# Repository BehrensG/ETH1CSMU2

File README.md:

# ETH1CSMU2
> Yet another poor man's SMU based on LT1970 Power Op Amp.

## What is a SMU ?

A Source Measurement Unit (SMU) is a versatile electronic instrument used in various applications, particularly in the field of electronics testing and characterization. It combines the functionalities of both a voltage source and a current measurement device.

## What is ETH1CSMU2 ?

ETH1CSMU2 is an ongoing hobby project focused on the development of a cost-effective Source Measurement Unit (SMU). The PCB has been designed in accordance with the Eurocard standard size, measuring 160x100 mm. It should be noted that the PCB is intended for integration with a Backplane, such as the [DIN41612_Backplane](https://github.com/BehrensG/DIN41612_Backplane), and is not intended for standalone operation (but it can be).
The PCB requires 24V DC supply. The device can sink and source voltage and current. Can generate a AC sine signal. The PCB includes pars of two ADCs for measurements. 2xADS868 designed the DC output mode, 2xAD7980 designed for AC output mode.

## Parameters

### DC
- Voltage output 11V (bipolar)
- Minimal set voltage step 1mV
- Current ranges 200uA, 2mA, 20mA and 200mA (bipolar)

### AC

- Sine wave generator
- Amplitude 6 V (bipolar)
- Offset 11 V (bipolar)
- Frequency 200 kHz

## Resources
- SCPI parser - https://github.com/j123b567/scpi-parser
- KiCAD - https://www.kicad.org
- STM32CubeIDE - https://www.st.com/en/development-tools/stm32cubeide.html
- POOR MAN'S SMU - https://poormanssmu.wordpress.com
- FreeRTOS - https://www.freertos.org/

## Images
<p align="center"> ETH1CSMU2 </p>

<p align="center"> Examples of the output voltages </p>

## Status

Project is ongoing. 

#### TBD:
1. Missing code for ADCs calibration.
2. Missing code for the trigger circuit. 
3. Need to improve the AC code.
4. More images in this README file.
5. Missing SCPI commands documentation.

**<span style="color:red">NOTE</span>**: When using KiCAD project it will be required to change the schematic and PCB libraries paths.

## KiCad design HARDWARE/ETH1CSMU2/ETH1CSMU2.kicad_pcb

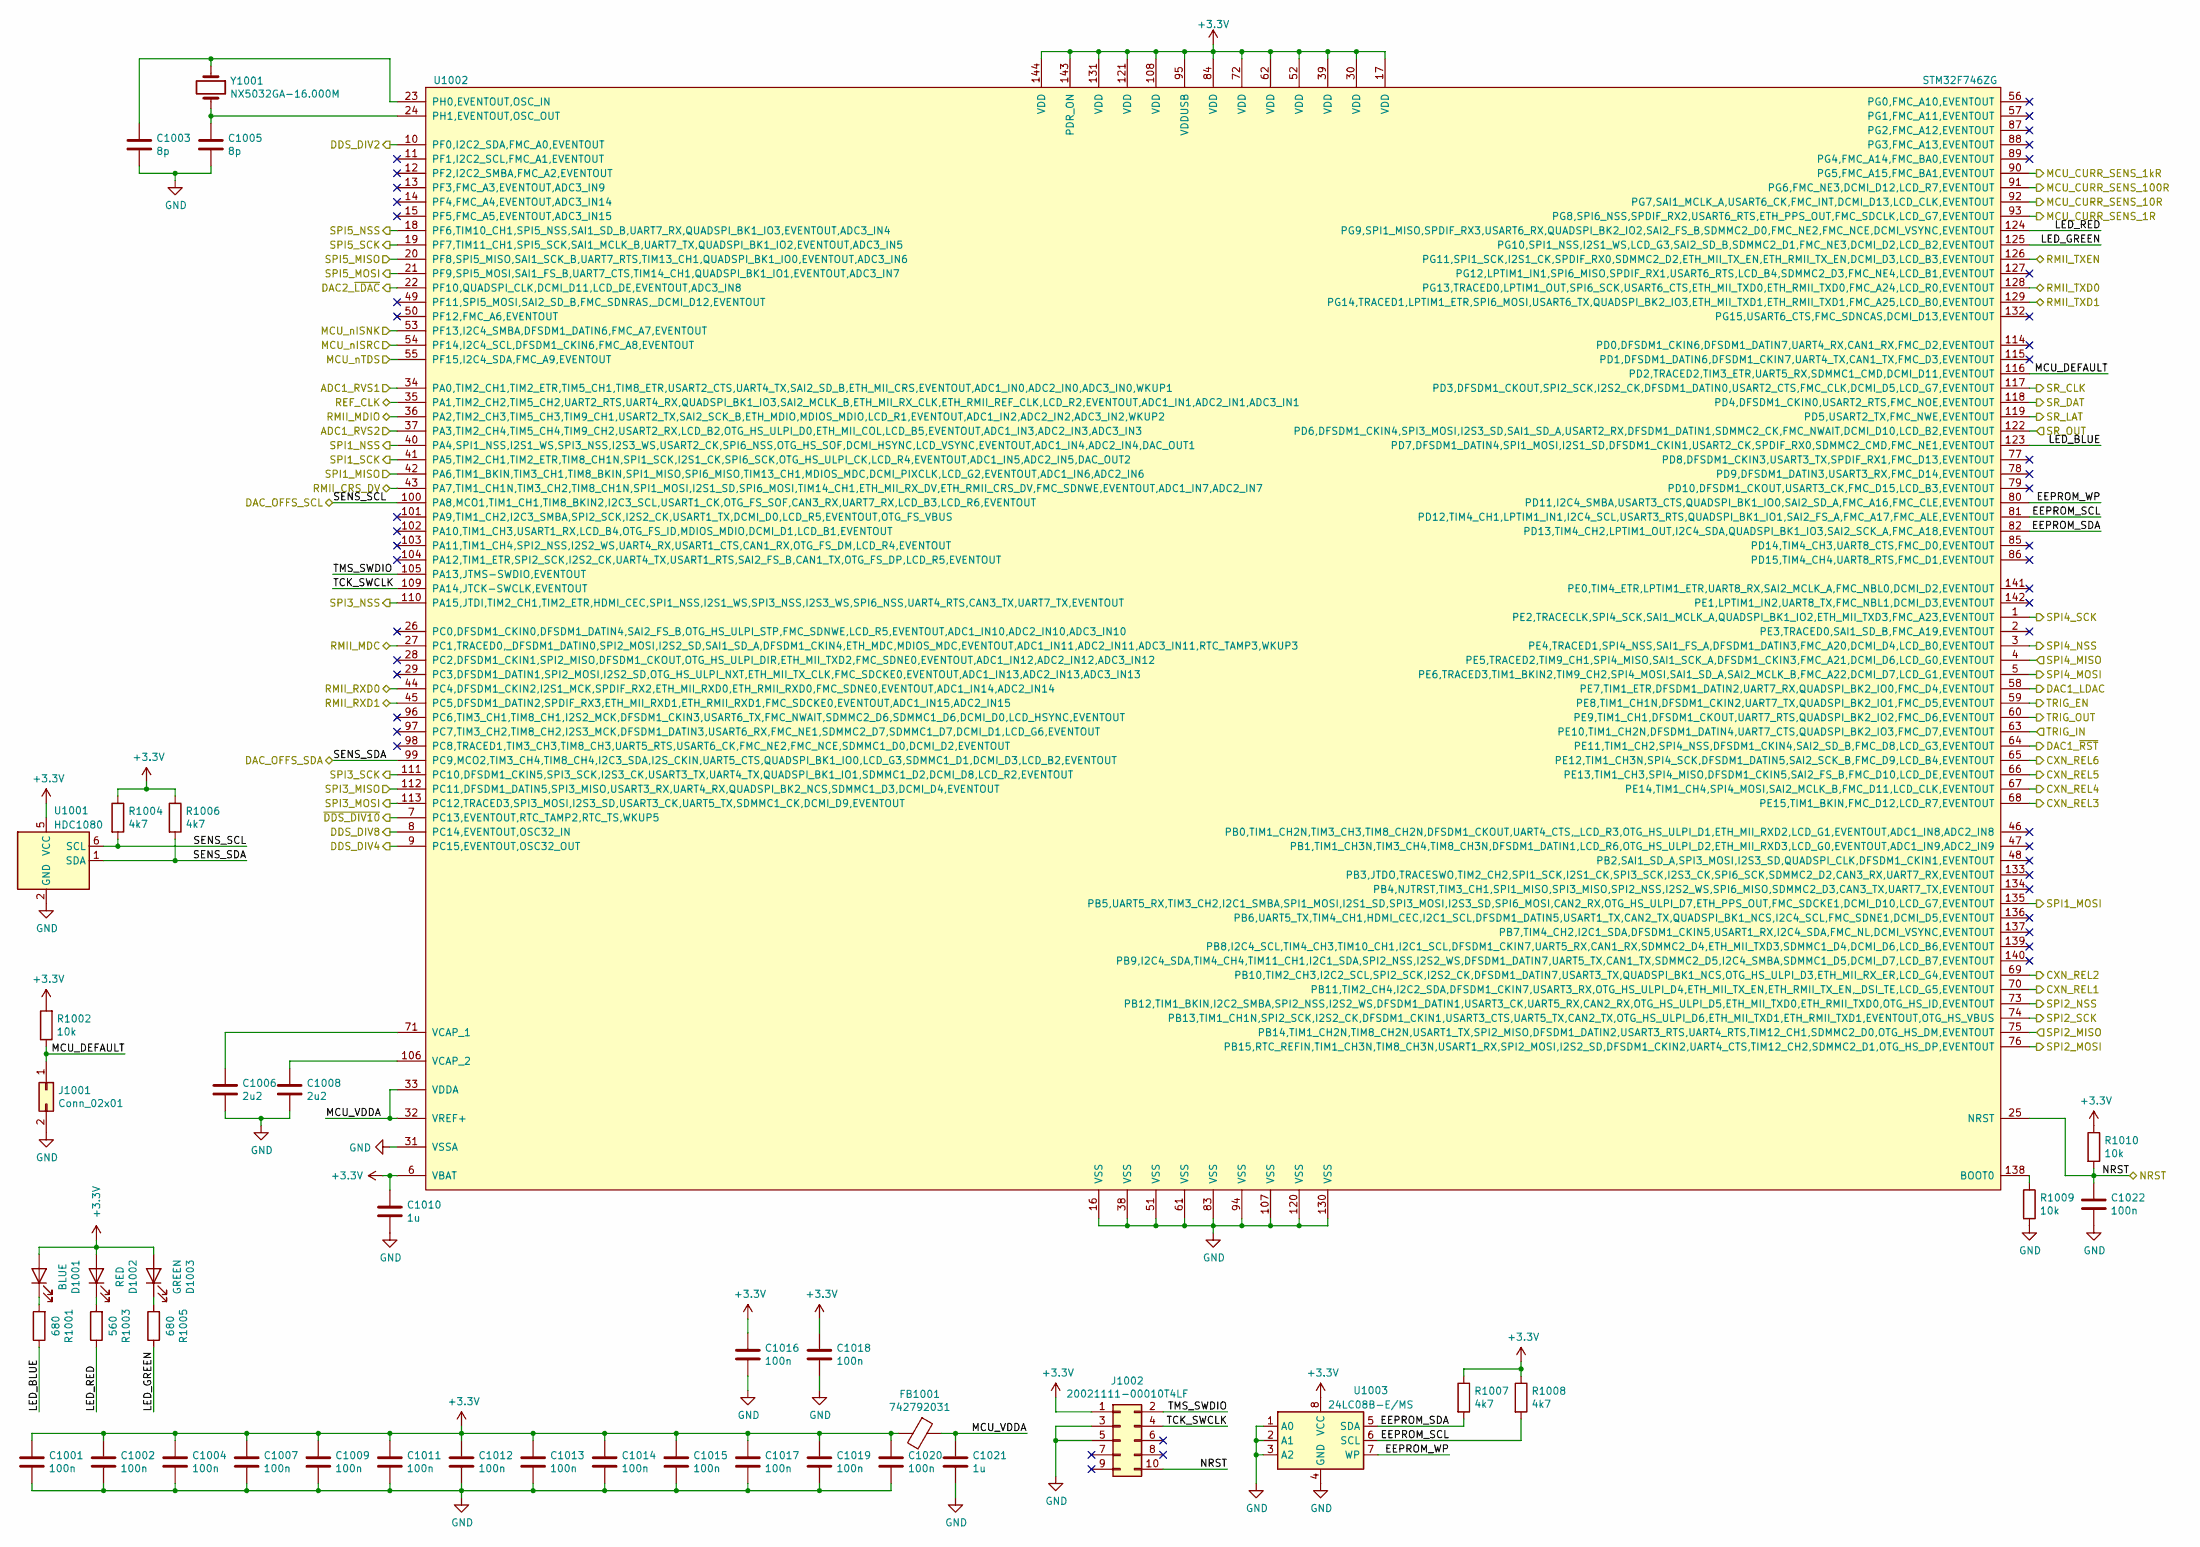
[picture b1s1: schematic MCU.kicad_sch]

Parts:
C1001, C1002, C1004, C1007, C1009, C1011, C1012, C1013, C1014, C1015, C1016, C1017, C1018, C1019, C1020, C1022: 100n; C_0603_1608Metric_Pad1.08x0.95mm_HandSolder
C1003, C1005: 8p; C_0603_1608Metric_Pad1.08x0.95mm_HandSolder
C1006, C1008: 2u2; C_0603_1608Metric_Pad1.08x0.95mm_HandSolder
C1010, C1021: 1u; C_0603_1608Metric_Pad1.08x0.95mm_HandSolder
D1001: BLUE; LED_0603_1608Metric_Pad1.05x0.95mm_HandSolder
D1002: RED; LED_0603_1608Metric_Pad1.05x0.95mm_HandSolder
D1003: GREEN; LED_0603_1608Metric_Pad1.05x0.95mm_HandSolder
FB1001: 742792031; L_0805_2012Metric_Pad1.15x1.40mm_HandSolder
J1001: Conn_02x01; PinHeader_1x02_P2.54mm_Vertical
J1002: 20021111-00010T4LF; PinHeader_2x05_P1.27mm_Vertical
R1001, R1005: 680; R_0603_1608Metric_Pad0.98x0.95mm_HandSolder
R1002, R1009, R1010: 10k; R_0603_1608Metric_Pad0.98x0.95mm_HandSolder
R1003: 560; R_0603_1608Metric_Pad0.98x0.95mm_HandSolder
R1004, R1006, R1007, R1008: 4k7; R_0603_1608Metric_Pad0.98x0.95mm_HandSolder
U1001: HDC1080; Texas_PWSON-N6
U1002: STM32F746ZG; TQFP-144_20x20mm_P0.5mm
U1003: 24LC08B-E/MS; MSOP-8_3x3mm_P0.65mm
Y1001: NX5032GA-16.000M; NX3225GD

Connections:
/Connect/CXN_REL1: U1002.70 (PB11,TIM2_CH4,I2C2_SDA,DFSDM1_CKIN7,USA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); also elsewhere on the board
/Connect/CXN_REL2: U1002.69 (PB10,TIM2_CH3,I2C2_SCL,SPI2_SCK,I2S2_CK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); also elsewhere on the board
/Connect/CXN_REL3: U1002.68 (PE15,TIM1_BKIN,FMC_D12,LCD_R7,EVENTOUT); also elsewhere on the board
/Connect/CXN_REL4: U1002.67 (PE14,TIM1_CH4,SPI4_MOSI,SAI2_MCLK_B,FMC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); also elsewhere on the board
/Connect/CXN_REL5: U1002.66 (PE13,TIM1_CH3,SPI4_MISO,DFSDM1_CKIN5,SA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); also elsewhere on the board
/Connect/CXN_REL6: U1002.65 (PE12,TIM1_CH3N,SPI4_SCK,DFSDM1_DATIN5,S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); also elsewhere on the board
/Control/SR_CLK: U1002.117 (PD3,DFSDM1_CKOUT,SPI2_SCK,I2S2_CK,DFSDM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); also elsewhere on the board
/Control/SR_DAT: U1002.118 (PD4,DFSDM1_CKIN0,USART2_RTS,FMC_NOE,EVE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); also elsewhere on the board
/Control/SR_LAT: U1002.119 (PD5,USART2_TX,FMC_NWE,EVENTOUT); also elsewhere on the board
/Control/SR_OUT: U1002.122 (PD6,DFSDM1_CKIN4,SPI3_MOSI,I2S3_SD,SAI1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); also elsewhere on the board
/Ethernet/MDIO: U1002.36 (PA2,TIM2_CH3,TIM5_CH3,TIM9_CH1,USART2_T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); also elsewhere on the board
/Ethernet/REF_CLK: U1002.35 (PA1,TIM2_CH2,TIM5_CH2,UART2_RTS,UART4_R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); also elsewhere on the board
/Ethernet/RMII_CRS_DV: U1002.43 (PA7,TIM1_CH1N,TIM3_CH2,TIM8_CH1N,SPI1_M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); also elsewhere on the board
/Ethernet/RMII_MDC: U1002.27 (PC1,TRACED0,_DFSDM1_DATIN0,SPI2_MOSI,I2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); also elsewhere on the board
/Ethernet/RMII_RXD0: U1002.44 (PC4,DFSDM1_CKIN2,I2S1_MCK,SPDIF_RX2,ETH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); also elsewhere on the board
/Ethernet/RMII_RXD1: U1002.45 (PC5,DFSDM1_DATIN2,SPDIF_RX3,ETH_MII_RXD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); also elsewhere on the board
/Ethernet/RMII_TXD0: U1002.128 (PG13,TRACED0,LPTIM1_OUT,SPI6_SCK,USART6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); also elsewhere on the board
/Ethernet/RMII_TXD1: U1002.129 (PG14,TRACED1,LPTIM1_ETR,SPI6_MOSI,USART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); also elsewhere on the board
/Ethernet/RMII_TXEN: U1002.126 (PG11,SPI1_SCK,I2S1_CK,SPDIF_RX0,SDMMC2_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); also elsewhere on the board
/Frontend/MCU_CURR_SENS_1R: U1002.93 (PG8,SPI6_NSS,SPDIF_RX2,USART6_RTS,ETH_P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); also elsewhere on the board
/Frontend/MCU_CURR_SENS_1kR: U1002.90 (PG5,FMC_A15,FMC_BA1,EVENTOUT); also elsewhere on the board
/Frontend/MCU_CURR_SENS_10R: U1002.92 (PG7,SAI1_MCLK_A,USART6_CK,FMC_INT,DCMI_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); also elsewhere on the board
/Frontend/MCU_CURR_SENS_100R: U1002.91 (PG6,FMC_NE3,DCMI_D12,LCD_R7,EVENTOUT); also elsewhere on the board
/Frontend/MCU_nISNK: U1002.53 (PF13,I2C4_SMBA,DFSDM1_DATIN6,FMC_A7,EVE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); also elsewhere on the board
/Frontend/MCU_nISRC: U1002.54 (PF14,I2C4_SCL,DFSDM1_CKIN6,FMC_A8,EVENT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); also elsewhere on the board
/Frontend/MCU_nTDS: U1002.55 (PF15,I2C4_SDA,FMC_A9,EVENTOUT); also elsewhere on the board
/MCU/ADC1_RVS1: U1002.34 (PA0,TIM2_CH1,TIM2_ETR,TIM5_CH1,TIM8_ETR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); also elsewhere on the board
/MCU/ADC1_RVS2: U1002.37 (PA3,TIM2_CH4,TIM5_CH4,TIM9_CH2,USART2_R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); also elsewhere on the board
/MCU/DAC1_LDAC: U1002.58 (PE7,TIM1_ETR,DFSDM1_DATIN2,UART7_RX,QUA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); also elsewhere on the board
/MCU/DAC1_~RST: U1002.64 (PE11,TIM1_CH2,SPI4_NSS,DFSDM1_CKIN4,SAI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); also elsewhere on the board
/MCU/DAC2_~LDAC: U1002.22 (PF10,QUADSPI_CLK,DCMI_D11,LCD_DE,EVENTO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); also elsewhere on the board
/MCU/DDS_DIV2: U1002.10 (PF0,I2C2_SDA,FMC_A0,EVENTOUT); also elsewhere on the board
/MCU/DDS_DIV4: U1002.9 (PC15,EVENTOUT,OSC32_OUT); also elsewhere on the board
/MCU/DDS_DIV8: U1002.8 (PC14,EVENTOUT,OSC32_IN); also elsewhere on the board
/MCU/EEPROM_SCL: R1008.2, U1002.81 (PD12,TIM4_CH1,LPTIM1_IN1,I2C4_SCL,USART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), U1003.6 (SCL)
/MCU/EEPROM_SDA: R1007.2, U1002.82 (PD13,TIM4_CH2,LPTIM1_OUT,I2C4_SDA,QUADS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), U1003.5 (SDA)
/MCU/EEPROM_WP: U1002.80 (PD11,I2C4_SMBA,USART3_CTS,QUADSPI_BK1_I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), U1003.7 (WP)
/MCU/LED_BLUE: R1001.1, U1002.123 (PD7,DFSDM1_DATIN4,SPI1_MOSI,I2S1_SD,DFS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)
/MCU/LED_GREEN: R1005.1, U1002.125 (PG10,SPI1_NSS,I2S1_WS,LCD_G3,SAI2_SD_B,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)
/MCU/LED_RED: R1003.1, U1002.124 (PG9,SPI1_MISO,SPDIF_RX3,USART6_RX,QUADS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)
/MCU/MCU_DEFAULT: J1001.1, R1002.1, U1002.116 (PD2,TRACED2,TIM3_ETR,UART5_RX,SDMMC1_CM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)
/MCU/MCU_VDDA: C1021.1, FB1001.1, U1002.32 (VREF+), U1002.33 (VDDA)
/MCU/NRST: C1022.1, J1002.10, R1010.2, U1002.25 (NRST); also elsewhere on the board
/MCU/SENS_SCL: R1004.2, U1001.6 (SCL), U1002.100 (PA8,MCO1,TIM1_CH1,TIM8_BKIN2,I2C3_SCL,U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); also elsewhere on the board
/MCU/SENS_SDA: R1006.2, U1001.1 (SDA), U1002.99 (PC9,MCO2,TIM3_CH4,TIM8_CH4,I2C3_SDA,I2S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); also elsewhere on the board
/MCU/SPI1_MISO: U1002.42 (PA6,TIM1_BKIN,TIM3_CH1,TIM8_BKIN,SPI1_M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); also elsewhere on the board
/MCU/SPI1_MOSI: U1002.135 (PB5,UART5_RX,TIM3_CH2,I2C1_SMBA,SPI1_MO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); also elsewhere on the board
/MCU/SPI1_NSS: U1002.40 (PA4,SPI1_NSS,I2S1_WS,SPI3_NSS,I2S3_WS,U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); also elsewhere on the board
/MCU/SPI1_SCK: U1002.41 (PA5,TIM2_CH1,TIM2_ETR,TIM8_CH1N,SPI1_SC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); also elsewhere on the board
/MCU/SPI2_MISO: U1002.75 (PB14,TIM1_CH2N,TIM8_CH2N,USART1_TX,SPI2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)
/MCU/SPI2_MOSI: U1002.76 (PB15,RTC_REFIN,TIM1_CH3N,TIM8_CH3N,USAR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); also elsewhere on the board
/MCU/SPI2_NSS: U1002.73 (PB12,TIM1_BKIN,I2C2_SMBA,SPI2_NSS,I2S2_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); also elsewhere on the board
/MCU/SPI2_SCK: U1002.74 (PB13,TIM1_CH1N,SPI2_SCK,I2S2_CK,DFSDM1_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); also elsewhere on the board
/MCU/SPI3_MISO: U1002.112 (PC11,DFSDM1_DATIN5,SPI3_MISO,USART3_RX,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)
/MCU/SPI3_MOSI: U1002.113 (PC12,TRACED3,SPI3_MOSI,I2S3_SD,USART3_C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); also elsewhere on the board
/MCU/SPI3_NSS: U1002.110 (PA15,JTDI,TIM2_CH1,TIM2_ETR,HDMI_CEC,SP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); also elsewhere on the board
/MCU/SPI3_SCK: U1002.111 (PC10,DFSDM1_CKIN5,SPI3_SCK,I2S3_CK,USAR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); also elsewhere on the board
/MCU/SPI4_MISO: U1002.4 (PE5,TRACED2,TIM9_CH1,SPI4_MISO,SAI1_SCK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); also elsewhere on the board
/MCU/SPI4_MOSI: U1002.5 (PE6,TRACED3,TIM1_BKIN2,TIM9_CH2,SPI4_MO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)
/MCU/SPI4_NSS: U1002.3 (PE4,TRACED1,SPI4_NSS,SAI1_FS_A,DFSDM1_D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); also elsewhere on the board
/MCU/SPI4_SCK: U1002.1 (PE2,TRACECLK,SPI4_SCK,SAI1_MCLK_A,QUADS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); also elsewhere on the board
/MCU/SPI5_MISO: U1002.20 (PF8,SPI5_MISO,SAI1_SCK_B,UART7_RTS,TIM1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)
/MCU/SPI5_MOSI: U1002.21 (PF9,SPI5_MOSI,SAI1_FS_B,UART7_CTS,TIM14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); also elsewhere on the board
/MCU/SPI5_NSS: U1002.18 (PF6,TIM10_CH1,SPI5_NSS,SAI1_SD_B,UART7_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); also elsewhere on the board
/MCU/SPI5_SCK: U1002.19 (PF7,TIM11_CH1,SPI5_SCK,SAI1_MCLK_B,UART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); also elsewhere on the board
/MCU/TCK_SWCLK: J1002.4, U1002.109 (PA14,JTCK-SWCLK,EVENTOUT)
/MCU/TMS_SWDIO: J1002.2, U1002.105 (PA13,JTMS-SWDIO,EVENTOUT)
/MCU/TRIG_EN: U1002.59 (PE8,TIM1_CH1N,DFSDM1_CKIN2,UART7_TX,QUA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); also elsewhere on the board
/MCU/TRIG_IN: U1002.63 (PE10,TIM1_CH2N,DFSDM1_DATIN4,UART7_CTS,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); also elsewhere on the board
/MCU/TRIG_OUT: U1002.60 (PE9,TIM1_CH1,DFSDM1_CKOUT,UART7_RTS,QUA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); also elsewhere on the board
/MCU/~DDS_DIV10: U1002.7 (PC13,EVENTOUT,RTC_TAMP2,RTC_TS,WKUP5); also elsewhere on the board
unnamed: C1003.1, U1002.23 (PH0,EVENTOUT,OSC_IN), Y1001.1
unnamed: C1005.1, U1002.24 (PH1,EVENTOUT,OSC_OUT), Y1001.2
unnamed: C1006.1, U1002.71 (VCAP_1)
unnamed: C1008.1, U1002.106 (VCAP_2)
unnamed: D1001.1 (K), R1001.2
unnamed: D1002.1 (K), R1003.2
unnamed: D1003.1 (K), R1005.2
unnamed: R1009.1, U1002.138 (BOOT0)

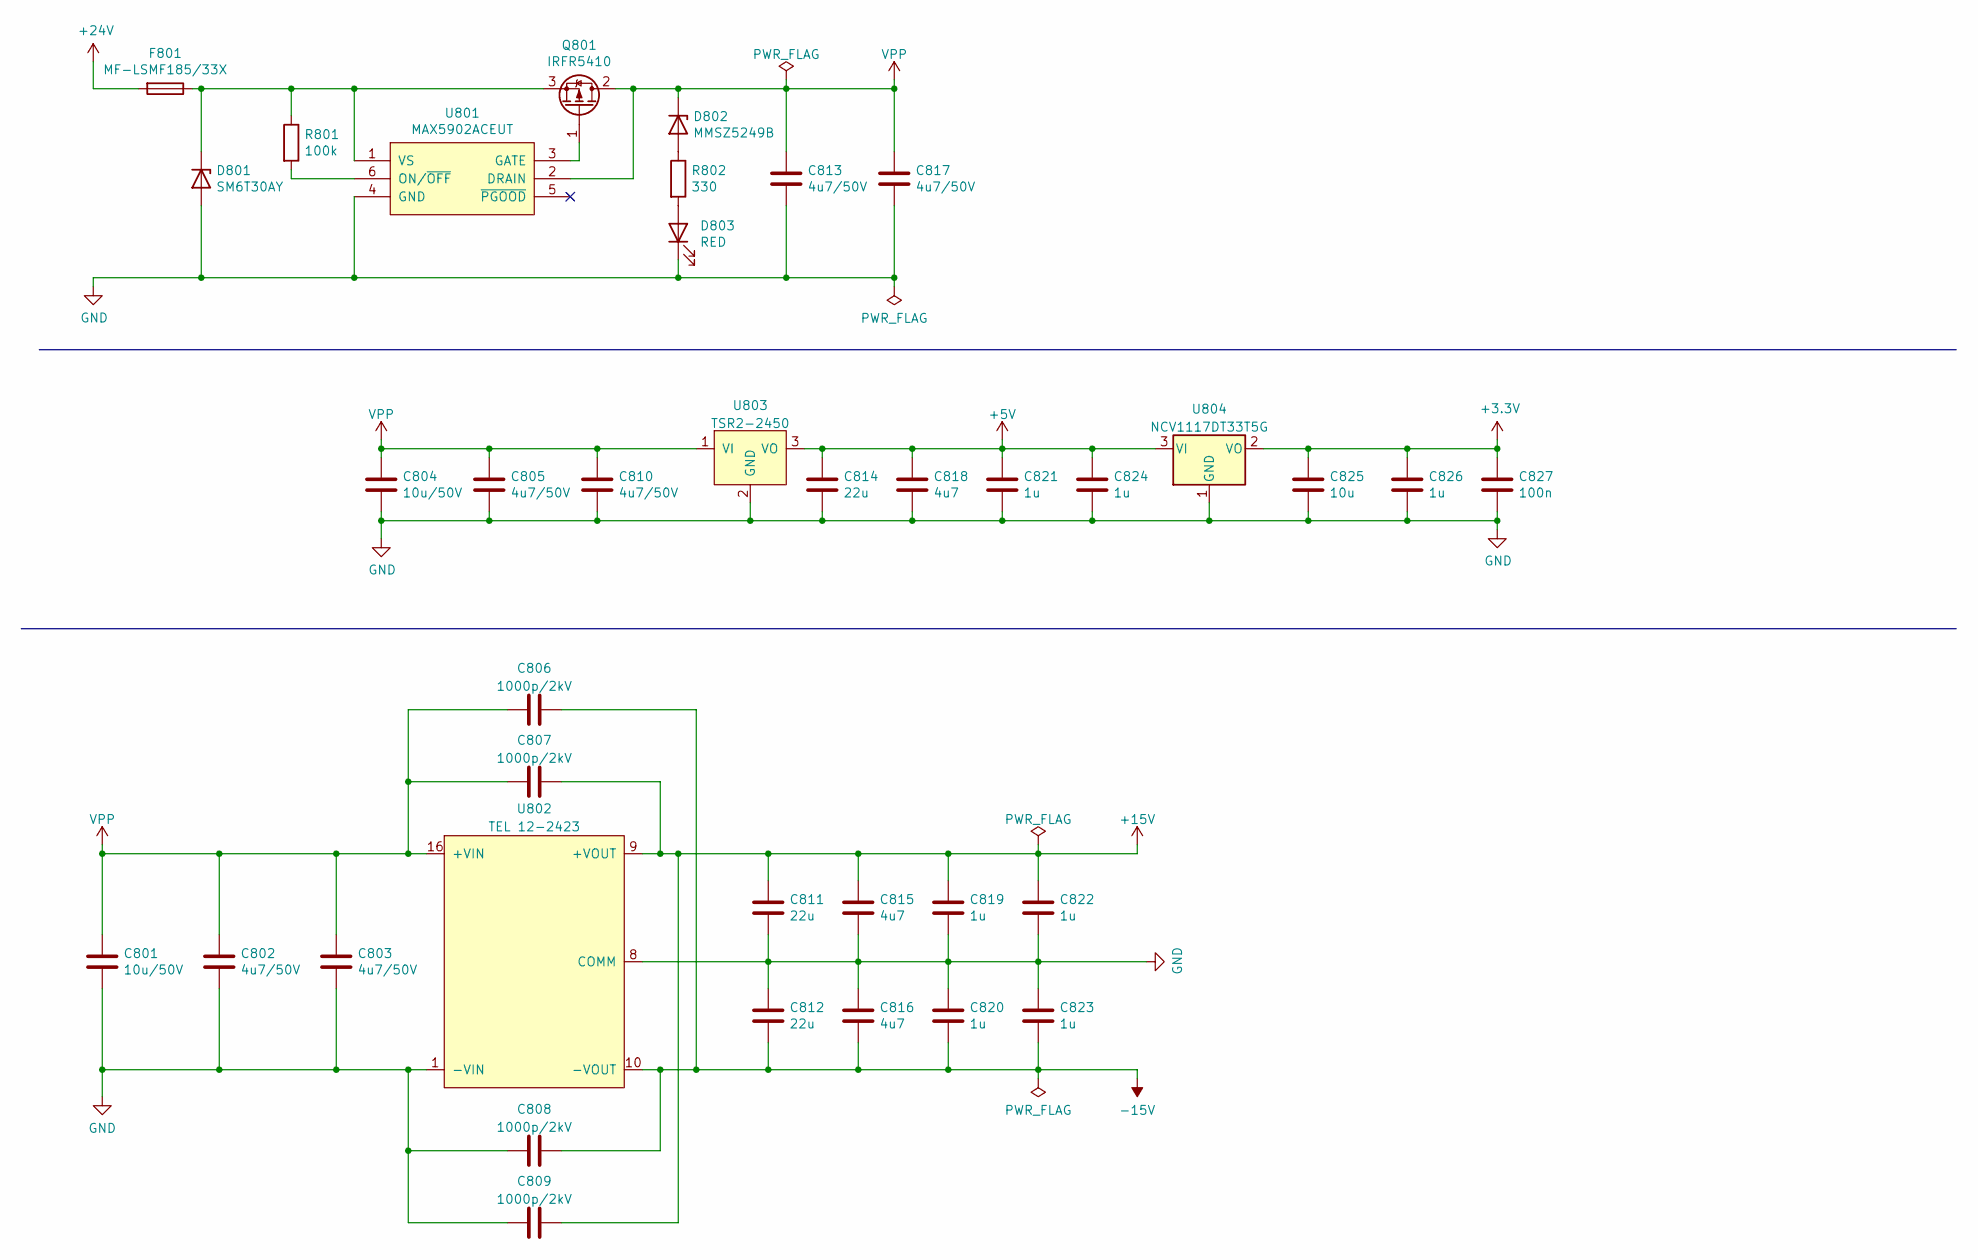
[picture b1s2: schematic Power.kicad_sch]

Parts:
C801, C804: 10u/50V; C_1206_3216Metric_Pad1.33x1.80mm_HandSolder
C802, C803, C805, C810, C813, C817: 4u7/50V; C_1206_3216Metric_Pad1.33x1.80mm_HandSolder
C806, C807, C808, C809: 1000p/2kV; C_1206_3216Metric_Pad1.33x1.80mm_HandSolder
C811, C812, C814: 22u; C_1206_3216Metric_Pad1.33x1.80mm_HandSolder
C815, C816, C818: 4u7; C_1206_3216Metric_Pad1.33x1.80mm_HandSolder
C819, C820, C821, C822, C823, C824, C826: 1u; C_1206_3216Metric_Pad1.33x1.80mm_HandSolder
C825: 10u; C_1206_3216Metric_Pad1.33x1.80mm_HandSolder
C827: 100n; C_1206_3216Metric_Pad1.33x1.80mm_HandSolder
D801: SM6T30AY; DO_214AA_REV
D802: MMSZ5249B; D_SOD-123
D803: RED; LED_0603_1608Metric_Pad1.05x0.95mm_HandSolder
F801: MF-LSMF185/33X; Fuse_SMD2920
Q801: IRFR5410; TO-252-2_Rectifier
R801: 100k; R_0603_1608Metric_Pad0.98x0.95mm_HandSolder
R802: 330; R_0603_1608Metric_Pad0.98x0.95mm_HandSolder
U801: MAX5902ACEUT; SOT-23-6_Handsoldering
U802: TEL 12-2423; TEL12-DUAL
U803: TSR2-2450; TSR2
U804: NCV1117DT33T5G; TO-252-2

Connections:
+24V: F801.2; also elsewhere on the board
unnamed: D801.1 (K), F801.1, Q801.3 (S), R801.1, U801.1 (VS)
unnamed: D802.2 (A), R802.1
unnamed: D803.2 (A), R802.2
unnamed: Q801.1 (G), U801.3 (GATE)
unnamed: R801.2, U801.6 (ON/~OFF)

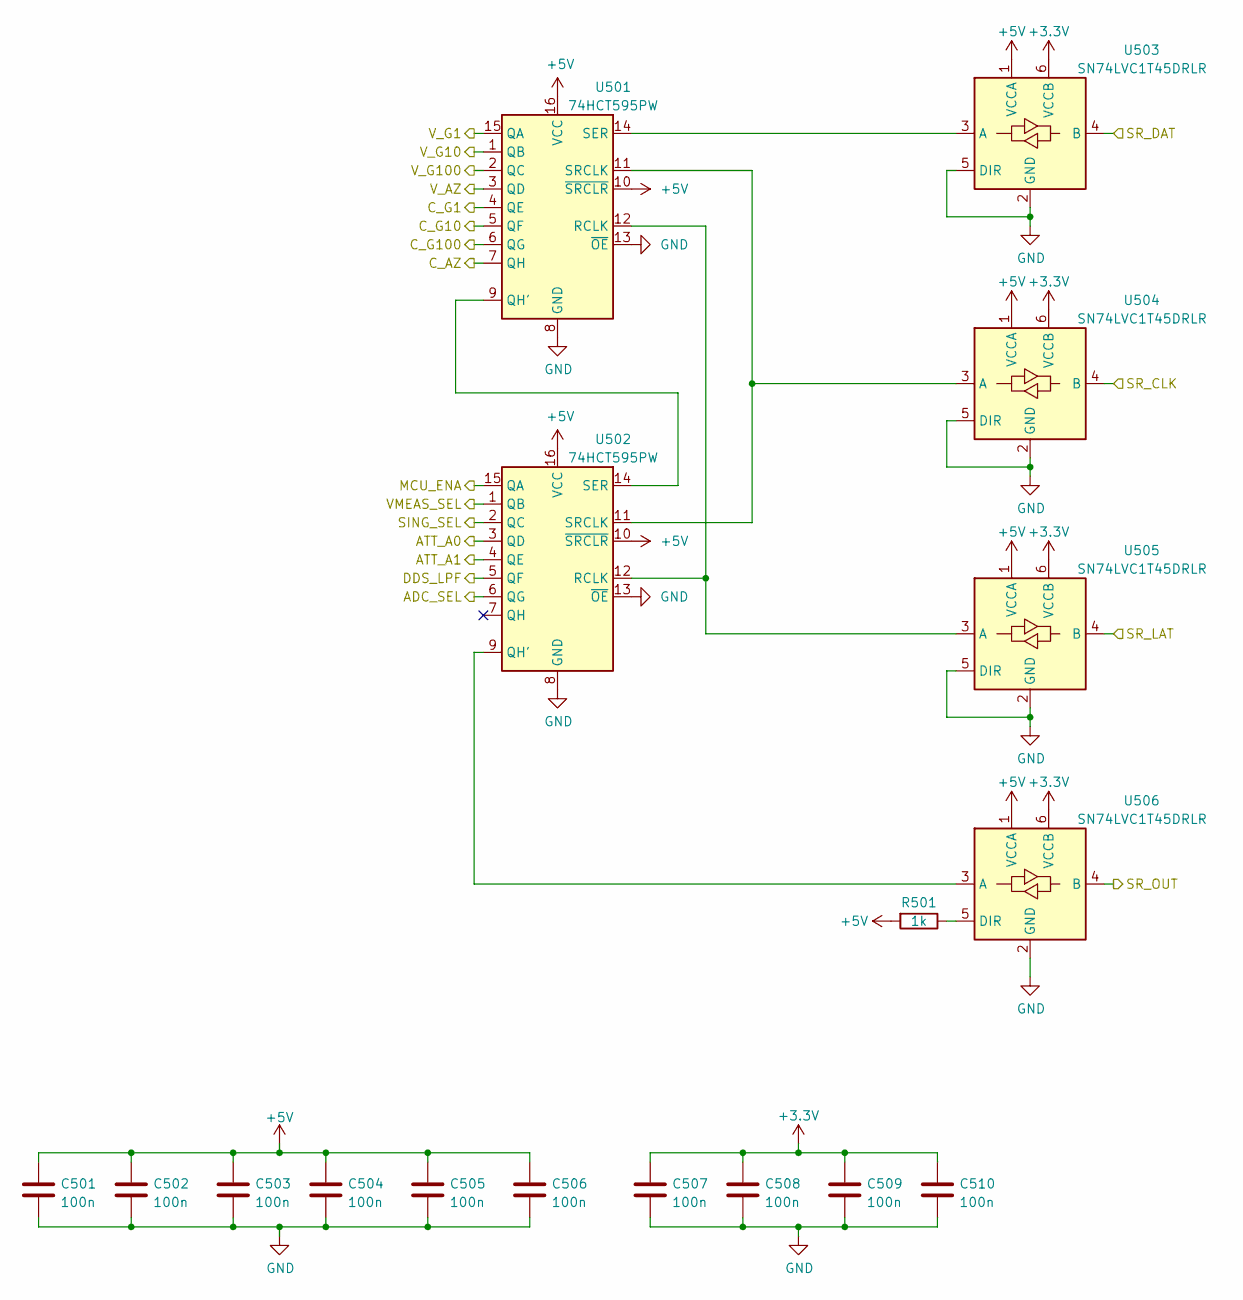
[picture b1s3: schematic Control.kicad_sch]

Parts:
C501, C502, C503, C504, C505, C506, C507, C508, C509, C510: 100n; C_0603_1608Metric_Pad1.08x0.95mm_HandSolder
R501: 1k; R_0603_1608Metric_Pad0.98x0.95mm_HandSolder
U501, U502: 74HCT595PW; TSSOP-16_4.4x5mm_P0.65mm
U503, U504, U505, U506: SN74LVC1T45DRLR; SOT-563

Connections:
/Control/ATT_A0: U502.3 (QD); also elsewhere on the board
/Control/ATT_A1: U502.4 (QE); also elsewhere on the board
/Control/C_AZ: U501.7 (QH); also elsewhere on the board
/Control/C_G1: U501.4 (QE); also elsewhere on the board
/Control/C_G10: U501.5 (QF); also elsewhere on the board
/Control/C_G100: U501.6 (QG); also elsewhere on the board
/Control/DDS_LPF: U502.5 (QF); also elsewhere on the board
/Control/MCU_ENA: U502.15 (QA); also elsewhere on the board
/Control/SING_SEL: U502.2 (QC); also elsewhere on the board
/Control/SR_CLK: U504.4 (B); also elsewhere on the board
/Control/SR_DAT: U503.4 (B); also elsewhere on the board
/Control/SR_LAT: U505.4 (B); also elsewhere on the board
/Control/SR_OUT: U506.4 (B); also elsewhere on the board
/Control/VMEAS_SEL: U502.1 (QB); also elsewhere on the board
/Control/V_AZ: U501.3 (QD); also elsewhere on the board
/Control/V_G1: U501.15 (QA); also elsewhere on the board
/Control/V_G10: U501.1 (QB); also elsewhere on the board
/Control/V_G100: U501.2 (QC); also elsewhere on the board
/Measure/ADC_SEL: U502.6 (QG); also elsewhere on the board
unnamed: R501.1, U506.5 (DIR)
unnamed: U501.9 (QH'), U502.14 (SER)
unnamed: U501.11 (SRCLK), U502.11 (SRCLK), U504.3 (A)
unnamed: U501.12 (RCLK), U502.12 (RCLK), U505.3 (A)
unnamed: U501.14 (SER), U503.3 (A)
unnamed: U502.9 (QH'), U506.3 (A)

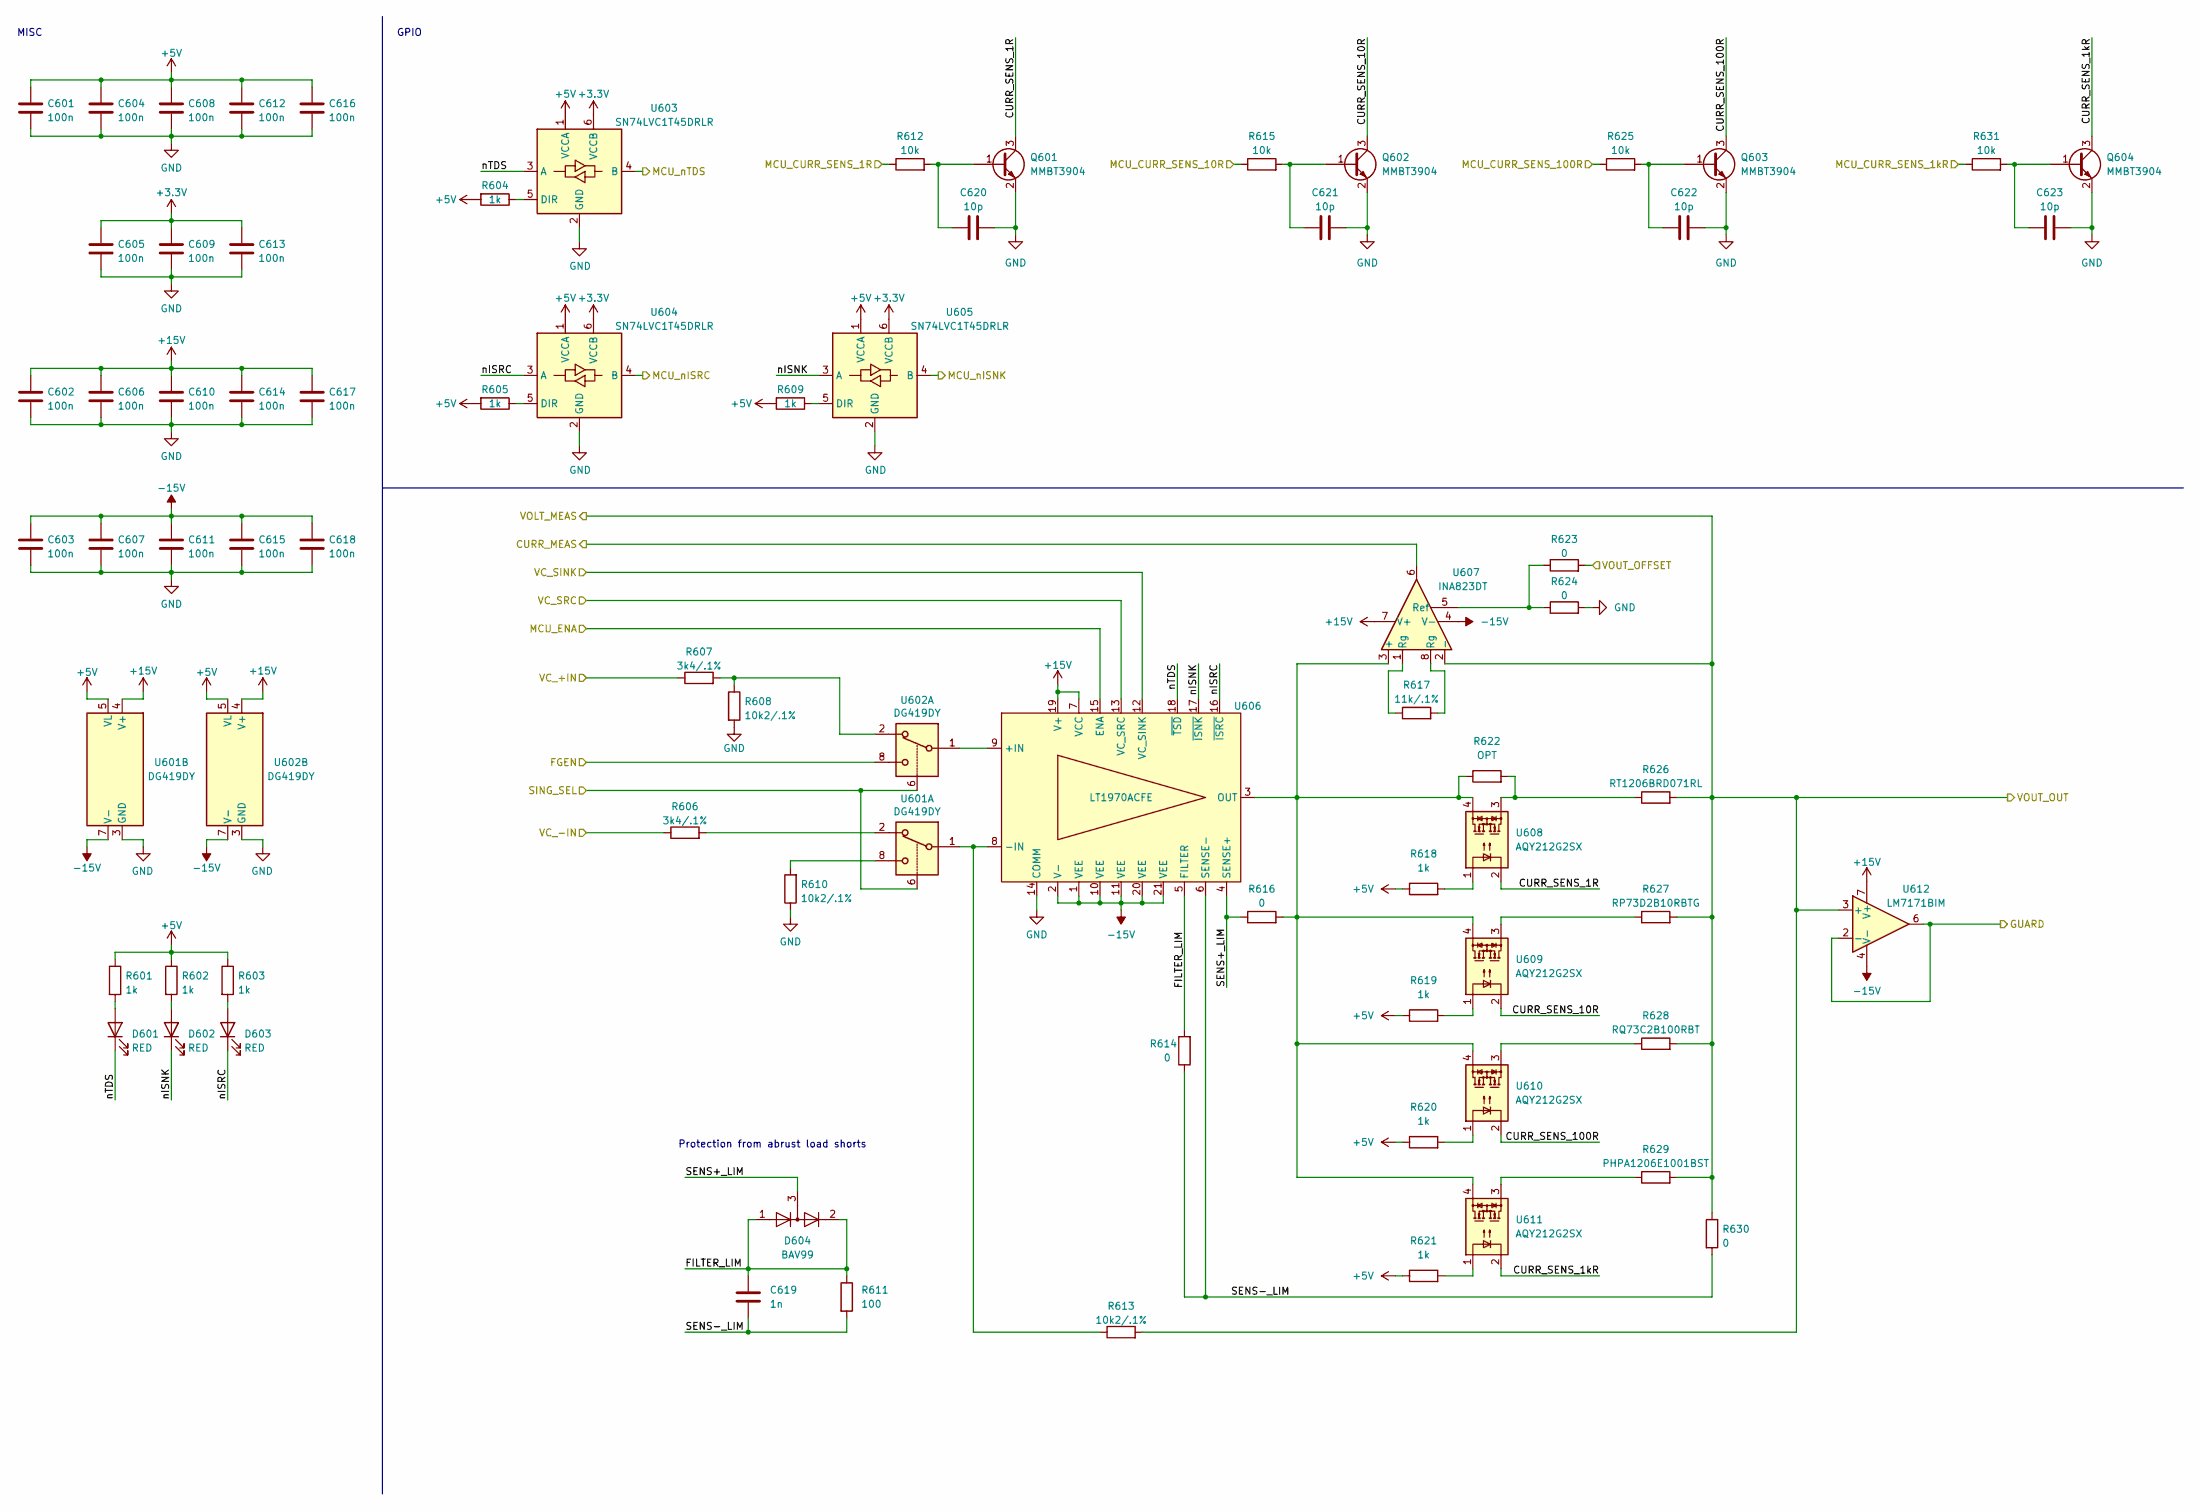
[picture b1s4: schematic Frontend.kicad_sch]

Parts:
C601, C602, C603, C604, C605, C606, C607, C608, C609, C610, C611, C612, C613, C614, C615, C616, C617, C618: 100n; C_0603_1608Metric_Pad1.08x0.95mm_HandSolder
C619: 1n; C_0603_1608Metric_Pad1.08x0.95mm_HandSolder
C620, C621, C622, C623: 10p; C_0603_1608Metric_Pad1.08x0.95mm_HandSolder
D601, D602, D603: RED; LED_0603_1608Metric_Pad1.05x0.95mm_HandSolder
D604: BAV99; SOT-23
Q601, Q602, Q603, Q604: MMBT3904; SOT-23
R601, R602, R603, R604, R605, R609, R618, R619, R620, R621: 1k; R_0603_1608Metric_Pad0.98x0.95mm_HandSolder
R606, R607: 3k4/.1%; R_0603_1608Metric_Pad0.98x0.95mm_HandSolder
R608, R610, R613: 10k2/.1%; R_0603_1608Metric_Pad0.98x0.95mm_HandSolder
R611: 100; R_0603_1608Metric_Pad0.98x0.95mm_HandSolder
R612, R615, R625, R631: 10k; R_0603_1608Metric_Pad0.98x0.95mm_HandSolder
R614, R616, R623, R624, R630: 0; R_0603_1608Metric_Pad0.98x0.95mm_HandSolder
R617: 11k/.1%; R_0603_1608Metric_Pad0.98x0.95mm_HandSolder
R622: OPT; R_0603_1608Metric_Pad0.98x0.95mm_HandSolder
R626: RT1206BRD071RL; R_1206_3216Metric_Pad1.30x1.75mm_HandSolder
R627: RP73D2B10RBTG; R_1206_3216Metric_Pad1.30x1.75mm_HandSolder
R628: RQ73C2B100RBT; R_1206_3216Metric_Pad1.30x1.75mm_HandSolder
R629: PHPA1206E1001BST; R_1206_3216Metric_Pad1.30x1.75mm_HandSolder
U601, U602: DG419DY; SOIC-8_3.9x4.9mm_P1.27mm
U603, U604, U605: SN74LVC1T45DRLR; SOT-563
U606: LT1970ACFE; HTSSOP-20-1EP_4.4x6.5mm_P0.65mm_EP3.4x6.5mm_ThermalVias
U607: INA823DT; SOIC-8_3.9x4.9mm_P1.27mm
U608, U609, U610, U611: AQY212G2SX; AQY212GS
U612: LM7171BIM; SOIC-8_3.9x4.9mm_P1.27mm

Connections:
/Connect/GUARD: U612.2 (-), U612.6; also elsewhere on the board
/Connect/VOUT_OUT: R613.2, R626.2, R627.2, R628.2, R629.2, R630.1, U607.2 (-), U612.3 (+); also elsewhere on the board
/Control/MCU_ENA: U606.15 (ENA); also elsewhere on the board
/Control/SING_SEL: U601.6, U602.6; also elsewhere on the board
/Frontend/CURR_MEAS: U607.6; also elsewhere on the board
/Frontend/CURR_SENS_1R: Q601.3 (C), U608.2
/Frontend/CURR_SENS_1kR: Q604.3 (C), U611.2
/Frontend/CURR_SENS_10R: Q602.3 (C), U609.2
/Frontend/CURR_SENS_100R: Q603.3 (C), U610.2
/Frontend/FGEN: U602.8; also elsewhere on the board
/Frontend/FILTER_LIM: C619.1, D604.1 (K), D604.2 (A), R611.1, R614.2, U606.5 (FILTER)
/Frontend/MCU_CURR_SENS_1R: R612.1; also elsewhere on the board
/Frontend/MCU_CURR_SENS_1kR: R631.1; also elsewhere on the board
/Frontend/MCU_CURR_SENS_10R: R615.1; also elsewhere on the board
/Frontend/MCU_CURR_SENS_100R: R625.1; also elsewhere on the board
/Frontend/MCU_nISNK: U605.4 (B); also elsewhere on the board
/Frontend/MCU_nISRC: U604.4 (B); also elsewhere on the board
/Frontend/MCU_nTDS: U603.4 (B); also elsewhere on the board
/Frontend/SENS+_LIM: D604.3 (K), R616.1, U606.4 (SENSE+)
/Frontend/SENS-_LIM: C619.2, R611.2, R614.1, R630.2, U606.6 (SENSE-)
/Frontend/VC_+IN: R607.1; also elsewhere on the board
/Frontend/VC_-IN: R606.1; also elsewhere on the board
/Frontend/VC_SINK: U606.12 (VC_SINK); also elsewhere on the board
/Frontend/VC_SRC: U606.13 (VC_SRC); also elsewhere on the board
/Frontend/VOUT_OFFSET: R623.2; also elsewhere on the board
/Frontend/nISNK: D602.1 (K), U605.3 (A), U606.17 (~ISNK)
/Frontend/nISRC: D603.1 (K), U604.3 (A), U606.16 (~ISRC)
/Frontend/nTDS: D601.1 (K), U603.3 (A), U606.18 (~TSD)
unnamed: C620.1, Q601.1 (B), R612.2
unnamed: C621.1, Q602.1 (B), R615.2
unnamed: C622.1, Q603.1 (B), R625.2
unnamed: C623.1, Q604.1 (B), R631.2
unnamed: D601.2 (A), R601.2
unnamed: D602.2 (A), R602.2
unnamed: D603.2 (A), R603.2
unnamed: R604.1, U603.5 (DIR)
unnamed: R605.1, U604.5 (DIR)
unnamed: R606.2, U601.2
unnamed: R607.2, R608.1, U602.2
unnamed: R609.1, U605.5 (DIR)
unnamed: R610.2, U601.8
unnamed: R613.1, U601.1, U606.8 (-IN)
unnamed: R616.2, R622.1, U606.3 (OUT), U607.3 (+), U608.4, U609.4, U610.4, U611.4
unnamed: R617.1, U607.1 (Rg)
unnamed: R617.2, U607.8 (Rg)
unnamed: R618.2, U608.1
unnamed: R619.2, U609.1
unnamed: R620.2, U610.1
unnamed: R621.2, U611.1
unnamed: R622.2, R626.1, U608.3
unnamed: R623.1, R624.1, U607.5 (Ref)
unnamed: R627.1, U609.3
unnamed: R628.1, U610.3
unnamed: R629.1, U611.3
unnamed: U602.1, U606.9 (+IN)

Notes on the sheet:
Protection from abrust load shorts
MISC
GPIO
